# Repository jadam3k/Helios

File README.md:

# Helios

I'm 17 and I'm building a solar-powered watering system for a greenhouse. Helios has two custom boards: **MPPT** handles the power side, and **DRIVER2** handles the pumps, sensors, screen and buttons. I wanted a project where I could learn PCB design and embedded programming while making something useful for growing plants.

The repository includes the KiCad projects, local libraries, firmware, manufacturing files, BOMs and board previews. The watering rules are an example for my setup. You can change the code to suit different sensors or watering zones, after checking their electrical requirements.

| MPPT | DRIVER2 |
| --- | --- |
|  |  |
| [Board documentation](Boards/MPPT/README.md) | [Board documentation](Boards/DRIVER2/README.md) |
| [Preview video](media/helios-mppt-preview.mp4) | [Preview video](media/helios-driver-preview.mp4) |

The images and videos show the CAD designs. I haven't tested the assembled system yet.

## Current progress

| Part | What's implemented | What's been checked |
| --- | --- | --- |
| DRIVER2 | Pump control, watering schedule, START/STOP/manual buttons, sensor handling, LCD, RTC and FRAM | Firmware previously built in STM32CubeIDE. Testing with real pumps and sensors is still needed. |
| MPPT | Measurements, actual PWM, current/voltage regulation, output-power P&O, charge completion/restart, switched-load control and watchdogs | Both configurations compiled for STM32L072CZ with Arduino STM32 core 3.1.0. The portable tests passed 25 checks and checked 88 PWM duty settings in both timer directions. Hardware tests are still needed. |

The supplied MPPT profile is for **protected 3S Li-ion**, with a **12.55 V charge target** and a **2 A converter-output limit**. Charging stays off until the battery and calibration confirmations in `Config.h` are set. Read the [firmware setup instructions](Boards/MPPT/firmware/README.md) before changing those settings. This profile is not for 12 V AGM or 4S LiFePO4 batteries.

## How the boards connect

```mermaid
flowchart LR
    PANEL[Solar panel] --> MPPT[MPPT board]
    BAT[Protected 3S battery] <--> MPPT
    MPPT -->|Switched battery supply| DRIVER[DRIVER2 board]
    MPPT --> USB[5 V accessories]
    SENS[Sensors] --> DRIVER
    BUTTONS[START / STOP / manual] --> DRIVER
    DRIVER --> LCD[16x2 LCD]
    DRIVER --> PUMPS[Four pumps]
    DRIVER --> AUX[Three AUX outputs]
    DRIVER --> AO[Optional analog output]
```

Connect MPPT **U5 pin 1** to DRIVER2 **CN1 pin 2**, and MPPT **U5 pin 2** to DRIVER2 **CN1 pin 1**. DRIVER2 receives switched battery voltage, rather than a regulated 12 V supply. Check the operating voltage of the actual pumps, sensors and other loads across the battery's range. The MPPT XT30 output is on a separate, unswitched rail.

Each MCU runs its own firmware. There is no data connection between the two boards in this version. The 8P8C connector is unused and is not an Ethernet interface.

## Example watering behaviour

- START arms automatic watering. STOP takes priority. Holding the manual button runs all four pumps until it is released.
- The example checks scheduled watering at 07:00 and 19:00. It can also respond to dry soil, the temperature switch and air humidity when that input is enabled.
- Automatic watering runs all four pumps together. It stops when soil reaches the configured target, if soil readings go stale, on a fault, or after the 60-second runtime limit.
- The three AUX outputs have an optional five-second on/off demonstration. The analog output and USB data functions are unused in the example.
- My sensor setup uses a KSD9700 NO 35°C switch, a JXCT JXBS-3001-TR-RS soil sensor and a Ropam RHT-2H humidity sensor. The Ropam input is disabled in the supplied DRIVER2 code. Check the board instructions before enabling it.

The temperature switch only reports whether its threshold has been crossed. It doesn't return a temperature in degrees.

## What can be changed

DRIVER2 has four pump outputs, three AUX outputs, two analog sensor ports, two digital/pulse ports, two RS485 ports and an analog output. The RTC, FRAM, current-sense circuits, LCD and buttons can also be used by your own code.

For example, you could split watering into independent zones, add flow meters, use more Modbus sensors or write a local settings menu. Those are possible extensions, not features already included in the example. The MPPT code also exposes its measurements and operating state for debugging. Its optional UART2 telemetry requires access to PA2/PA3; no dedicated debug socket is fitted for those pins.

## Open and build

1. Open a board's `.kicad_pro` file in KiCad 10. Keep its local `libs/` folder and library tables next to it.
2. Import `Boards/DRIVER2/Filmware` into STM32CubeIDE to build the watering controller. The existing `Filmware` spelling is kept for compatibility with the project paths.
3. Open [HeliosMPPT.ino](Boards/MPPT/firmware/HeliosMPPT/HeliosMPPT.ino) in Arduino IDE 2. Install **STM32 MCU based boards 3.1.0**, select **Generic STM32L0 series → Generic L072CZTx**, and follow the [MPPT instructions](Boards/MPPT/firmware/README.md).
4. Follow [setup and wiring](docs/SETUP.md) for programming, configuration and the first hardware checks.

[Download the complete MPPT firmware](Boards/MPPT/firmware/HeliosMPPT-full.zip) · [Read all MPPT source files](Boards/MPPT/firmware/COMPLETE_SOURCE.txt) · [Build results](Boards/MPPT/firmware/BUILD_RESULTS.txt)

## Parts and cost

The [combined BOM](BOM.csv) includes both board lists and the external parts needed for an installation. Detailed tables are in the [DRIVER2 README](Boards/DRIVER2/README.md#bill-of-materials) and [MPPT README](Boards/MPPT/README.md#bill-of-materials). Both boards also keep their original manufacturing BOMs.

| Item | Quantity / cost status |
| --- | --- |
| DRIVER2 board components | 318 instances across 69 manufacturing-BOM rows |
| MPPT source components | 112 instances across 57 grouped rows, including test points |
| Priced subtotal | USD 185.5548, using priced rows from both boards, checked on November 19, 2026 |
| Full system cost | Incomplete: some MPPT parts, external devices, PCB fabrication, assembly, shipping and taxes are not priced |

The priced subtotal is not a full project quote. Missing costs are left blank or marked `n.a.` in the BOM. Some MPPT supplier selections are still missing. Final battery capacity, pump models, fuse selection and supplier quotes still need to be completed before ordering a full system.

## Power budget

Use actual measurements to size the panel and battery:

```text
Daily energy = standby power × 24 h + sum(load power × daily runtime)
Nominal battery energy = nominal battery voltage × capacity in Ah
```

As an example, 2 W standby plus four 6 W pumps running for ten minutes uses about **52 Wh/day**. A hypothetical 3S pack rated 11.1 V / 12 Ah stores about 133 Wh nominally. The usable energy is lower and depends on the cells, operating limits, temperature and losses. These numbers are examples, not measured Helios consumption or a final battery specification.

## Files

| Location | Contents |
| --- | --- |
| [Boards/MPPT/](Boards/MPPT/) | Power-board KiCad sources, libraries, firmware and documentation |
| [Boards/DRIVER2/](Boards/DRIVER2/) | Watering-controller KiCad sources, libraries and STM32CubeIDE project |
| [docs/SETUP.md](docs/SETUP.md) | Wiring, build and first-start instructions |
| [BOM.csv](BOM.csv) | Combined parts list and cost status |
| [CREDITS.md](CREDITS.md) | Development assistance and third-party dependencies |
| `media/` | Main renders and preview videos |

Source files are included for review and development. A project-wide license has not been selected. Third-party files keep their own license terms.

## A few thoughts at the end

I'm really happy with how Helios has turned out so far. This project taught me a lot about PCB design, power electronics and programming microcontrollers. It took a lot of hours, and there were plenty of things I had to learn along the way. Looking through the files now, it's nice to see how much work has come together. I hope it passes review and that the effort behind it comes through.

For anyone reviewing or analysing the project: I was given permission in **#PIXL-HELP** to use AI for translation. So yes, parts of the README and journals might have an "AI vibe" because AI helped translate them into English. I also received permission from staff in the same channel to write journals about the programming work. Development assistance is described in [CREDITS.md](CREDITS.md).

I also used AI to help create the 3D animations. Those animations were not included in my journals or counted towards my logged hours. The time spent preparing the BOM, writing the README and organising the project files was not included in my logged hours either.

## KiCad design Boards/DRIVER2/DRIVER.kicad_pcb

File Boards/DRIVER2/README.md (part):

# Helios DRIVER2

I designed this board to run the watering system in my Helios greenhouse project. The four-layer board is about 117 × 91 mm and uses an STM32F429ZGT6. It switches four 12 V pumps, has three spare 12 V outputs, and takes up to six sensors through M8 connectors. My example firmware uses three sensors. You can change the code for your own setup as long as your sensors match the port voltages and interfaces.

The firmware builds in STM32CubeIDE. I still need to test it on the board with real sensors and pumps.

[System overview](../../README.md) · [Wiring and setup](../../docs/SETUP.md) · [MPPT board](../MPPT/README.md)

## Project files

| File or folder | What's inside |
| --- | --- |
| [DRIVER.kicad_pro](DRIVER.kicad_pro) | Open this in KiCad 10. The schematic, board and design rules are next to it. |
| [libs/](libs/) | Local symbols, footprints and 3D models. Keep this folder next to the KiCad project. |
| [Schematic PDF](docs/DRIVER.pdf) · [STEP model](docs/DRIVER.step) | Schematic and mechanical model. |
| [production/](production/) | Gerber ZIP, BOM CSV, component positions and other fabrication files. |
| [Interactive BOM](bom/ibom.html) | Find parts on the board. |
| [Filmware/](Filmware/) | STM32CubeIDE project, CubeMX configuration, C source and STM32 HAL. |
| [Filmware.elf](Filmware/artifacts/Filmware.elf) | Debug build. |
| [3D preview](media/helios-driver-3d.png) · [Video](media/helios-driver-preview.mp4) | Board preview and video. |

## Hardware

| Block | Parts and purpose |
| --- | --- |
| Power | 12 V DC input, separate feeds for logic and loads, and 5 V and 3.3 V rails. |
| Pumps and AUX | Four PUMP and three AUX outputs. Each uses a TPS1H100B-Q1 high-side switch and has a current-sense circuit. Check pump startup current, supply capacity, wiring and board temperature under load. |
| Sensors | Six M8 ports. SENS1–2 are analog, SENS3–4 are digital or pulse inputs, and SENS5–6 use THVD1410 RS-485 transceivers. Pin 1 supplies 5 V on SENS1–4 and 12 V on SENS5–6. |
| AO1 | 0–10 V analog output with an OPA197. |
| Clock and memory | Battery-backed DS3231 RTC and FM24W256 FRAM on I²C1. |
| Display and controls | 16×2 LCD1602 with a PCF8574T backpack on I²C2, a level shifter, and a separate three-button connector. |
| Debug and supervision | SWD, power status inputs, TPS3431 watchdog, TPS3808 reset supervisor and USB-C. |

### Pinout

| Connector | Pins |
| --- | --- |
| CN1 | 1 GND, 2 +12 V DC. |
| CN8 / CN9 / CN7 / CN10 | PUMP1 / PUMP2 / PUMP3 / PUMP4. Pin 1 GND, pin 2 switched +12 V. |
| CN2 / CN3 / CN4 | AUX1 / AUX2 / AUX3. Pin 1 GND, pin 2 switched +12 V. |
| CN5 | Pin 1 GND, pin 2 AO1. |
| CN6 SWD | 1 VTref 3.3 V, 2 SWDIO, 3/5/9 GND, 4 SWCLK, 6 SWO, 10 NRST. |
| U12 LCD | JST-XH B4B-XH-A. 1 +5 V, 2 GND, 3 SDA, 4 SCL. Match the wires to the labels on your LCD module. |
| U10 buttons | 1 GND, 2 START (PF14), 3 STOP (PF15), 4 manual watering (PG0). Each momentary button shorts its input to GND when pressed. |
| M8 SENS1–6 | 1 power, 2 SIG2, 3 GND, 4 SIG1. For RS-485, pin 2 is B and pin 4 is A on this board. |

## Firmware

[main.c](Filmware/Core/Src/main.c) handles watering, the LCD, RTC, FRAM, sensor readings and outputs. [buttons.c](Filmware/Core/Src/buttons.c) handles the three buttons. The pin assignments and peripheral settings are in [Filmware.ioc](Filmware/Filmware.ioc).

- **START** arms automatic watering. **STOP** takes priority. Hold the third button to run all four pumps manually.
- The controller checks the schedule at **07:00 and 19:00**. Between those times it can also start if the soil reads 35% or less for five samples, the temperature switch stays closed for about 5 seconds, or air humidity is 40% or less once that input is enabled. Daytime watering requires a valid soil reading below 55% and a 30-minute cooldown between runs.
- Automatic watering runs all four pumps and stops after three consecutive soil readings of at least 55%, if the soil reading goes stale, or after 60 seconds. A power fault shuts off the outputs.
- Before starting a scheduled run, the firmware saves the date in FRAM. The morning and evening slots have separate CRC-checked records so a restart won't repeat a run. PE3 keeps FRAM write protection high between writes.
- The LCD uses I²C address `0x27` (7-bit) and switches pages every 4 seconds. To try the AUX demo, set `aux_demo_request = 1` in the debugger while stopped. The three AUX outputs switch every 5 seconds. STOP or a power fault ends the demo. The example leaves AO1 and USB data unused.

### Sensors in my setup

| Measurement | Sensor and port | Connection |
| --- | --- | --- |
| Temperature threshold | KSD9700 NO 35°C on SENS3 (DIGITAL 1) | Dry contact between SIG1 (pin 4) and GND (pin 3). The STM32 reads it on PD9. |
| Soil moisture | JXCT JXBS-3001-TR-RS on SENS5 (RS485 1) | Modbus RTU, address 1, 9600 baud, 8N1, register `0x0002`. USART2 uses PD5 for TX, PD6 for RX and PD4 for direction. [JXCT manual](https://sourcewell.in/wp-content/uploads/2022/08/RS485-Soil-Temperature-and-Humidity-Sensor-JX-Instruction-Manual.pdf) |
| Air humidity | Ropam RHT-2H, EAN 5907565617733, on SENS1 (ANALOG 1) | RH-10V goes to SIG1 (pin 4). Power the sensor from a separate 12 V feed with a shared GND. [Ropam manual](https://ropam.com.pl/wsparcie/wp-content/uploads/2018/09/rht-2_i_pl.pdf) |

## Build and setup

Import [Filmware](Filmware/) as an existing STM32CubeIDE project and build it. Keep the `Core`, `Drivers`, linker scripts and IDE project files together. The peripheral configuration is [Filmware.ioc](Filmware/Filmware.ioc). The existing `Filmware` folder spelling is intentional so the saved paths keep working.

Program through CN6 SWD using the pinout above. Check the RTC date/time, LCD address, sensor configuration and STOP behaviour before connecting the actual pumps. The firmware has been built, but I still need to test the assembled board with its sensors and loads.

The example uses three sensor ports. The other ports remain available for your own code. `AIR_RH_ENABLED` is 0 in the supplied source; leave it off until the Ropam input's voltage scaling is suitable and calibrated. Read [system setup](../../docs/SETUP.md) before powering DRIVER2 from MPPT: that connection carries battery voltage.

## Bill of materials

[Original manufacturing BOM](production/bom.csv) · [Combined system BOM](../../BOM.csv)

The tables use direct supplier product links. Prices are USD per component at the stated quantity tier, checked on **November 19, 2026**. Costs use the required component quantities; the final cart can cost more because of minimum order quantities. Shipping, tax, fabrication and assembly are separate.

| References | Qty | Board value | Manufacturer part | Supplier | USD/part | Price tier |
| --- | ---: | --- | --- | --- | ---: | ---: |
| BT1 | 1 | BS-2-1 | BS-2-1 | [C2895401](https://jlcpcb.com/partdetail/BS-2-1/C2895401) | — | — |
| C1, C11, C23, C25, C39, C62, C63, C70, C71, C82, C88 | 11 | 1uF | CL10A105KB8NNNC | [C15849](https://www.lcsc.com/product-detail/C15849.html) | 0.0093 | 50 |
| C10, C12, C13, C2, C20, C24, C27, C31, C33, C34, C36, C37, C38, C40, C41, C42, C43, C44, C45, C46, C47, C48, C5, C53, C55, C57, C58, C59, C60, C65, C66, C67, C68, C69, C72, C73, C74, C75, C76, C79, C8, C80, C81, C87, C89, C9, C92, C93 | 48 | 100nF | CC0603KRX7R9BB104 | [C14663](https://www.lcsc.com/product-detail/C14663.html) | 0.0061 | 100 |
| C14, C15, C21, C22, C32, C35, C83, C84, C85, C86, C94, C95, C96, C97 | 14 | 10nF | CL10B103KB8NNNC | [C1589](https://www.lcsc.com/product-detail/C1589.html) | 0.0071 | 50 |
| C16, C17, C18, C19, C28, C29 | 6 | 22uF | CL31A226KAHNNNE | [C12891](https://www.lcsc.com/product-detail/C12891.html) | 0.1038 | 20 |
| C26, C3, C30, C4, C6, C7, C77, C78, C90, C91 | 10 | 10uF | CL31A106KBHNNNE | [C13585](https://www.lcsc.com/product-detail/C13585.html) | 0.1238 | 10 |
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
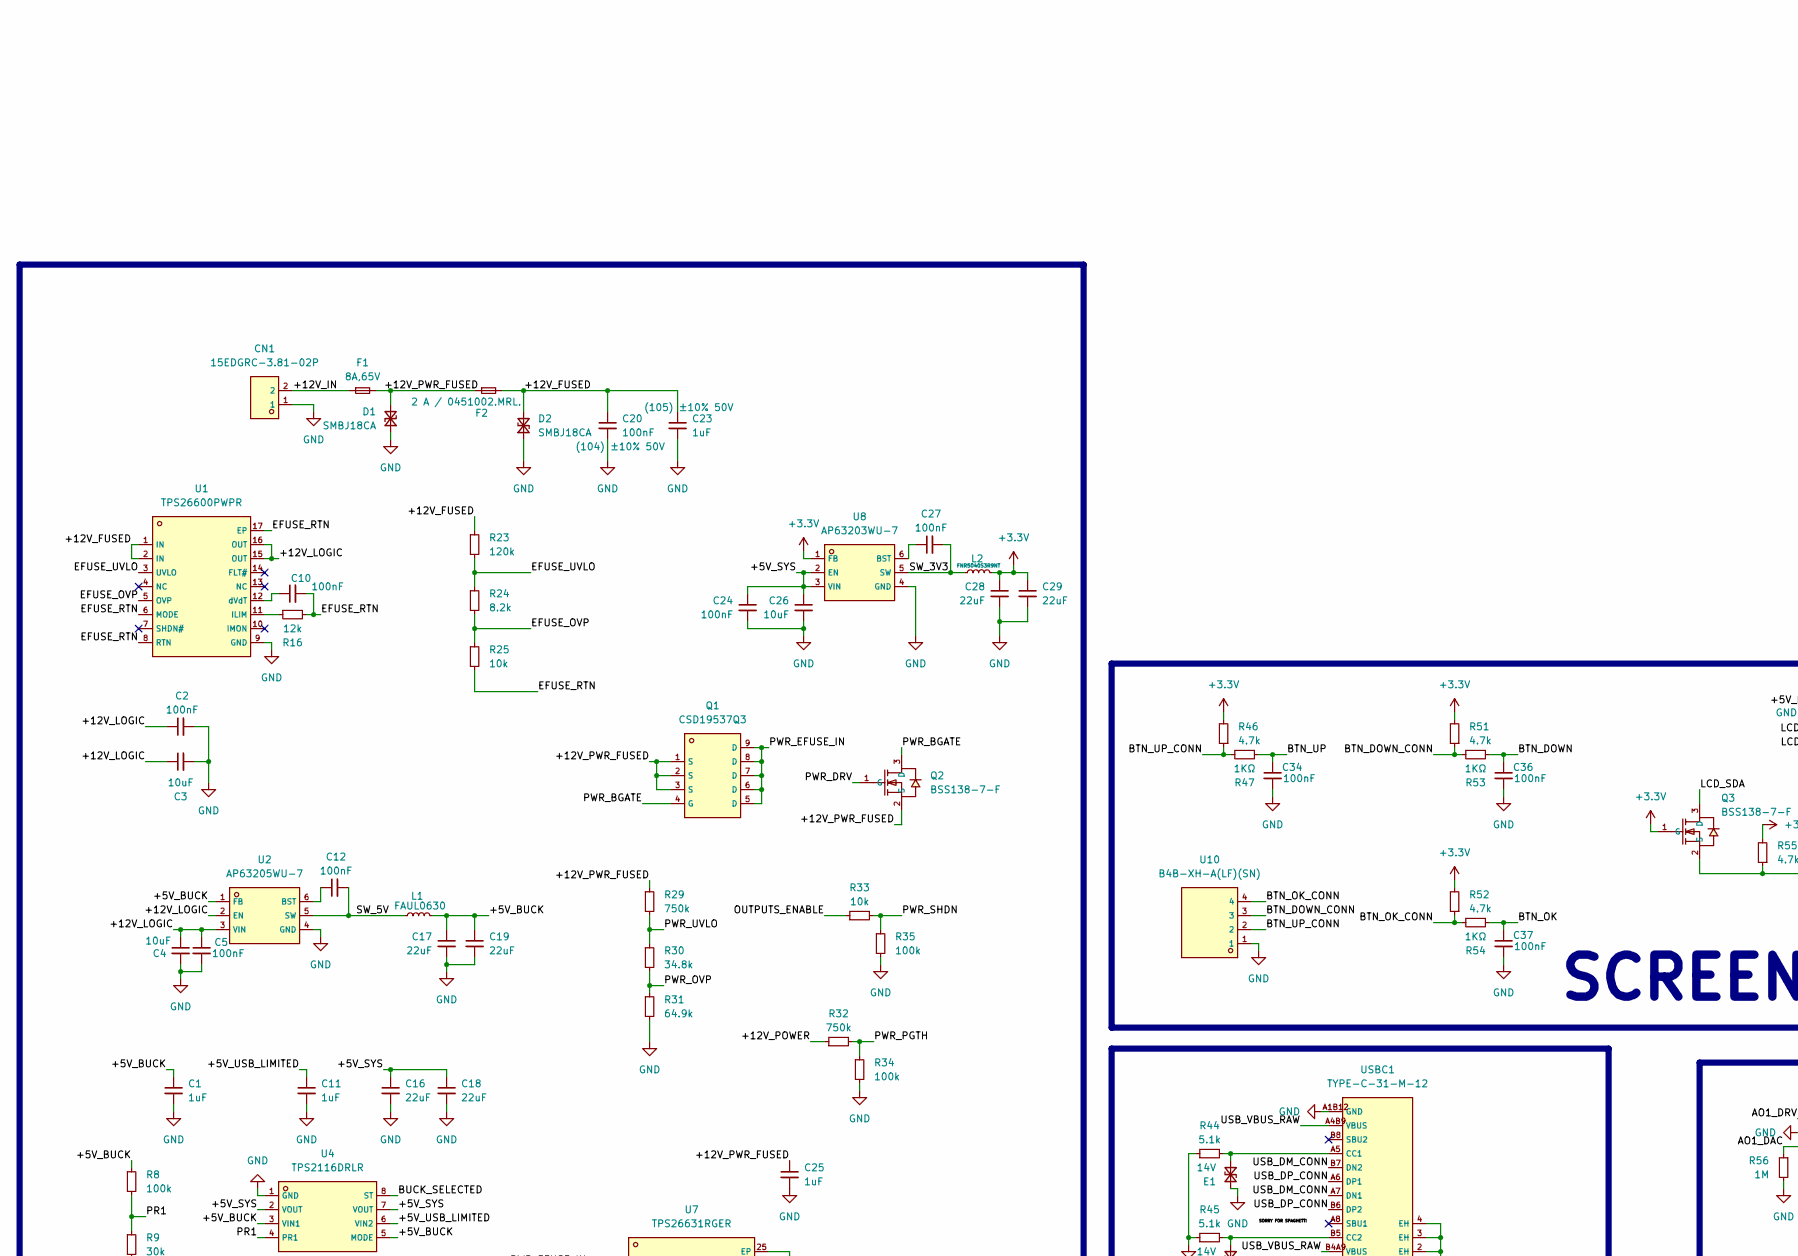
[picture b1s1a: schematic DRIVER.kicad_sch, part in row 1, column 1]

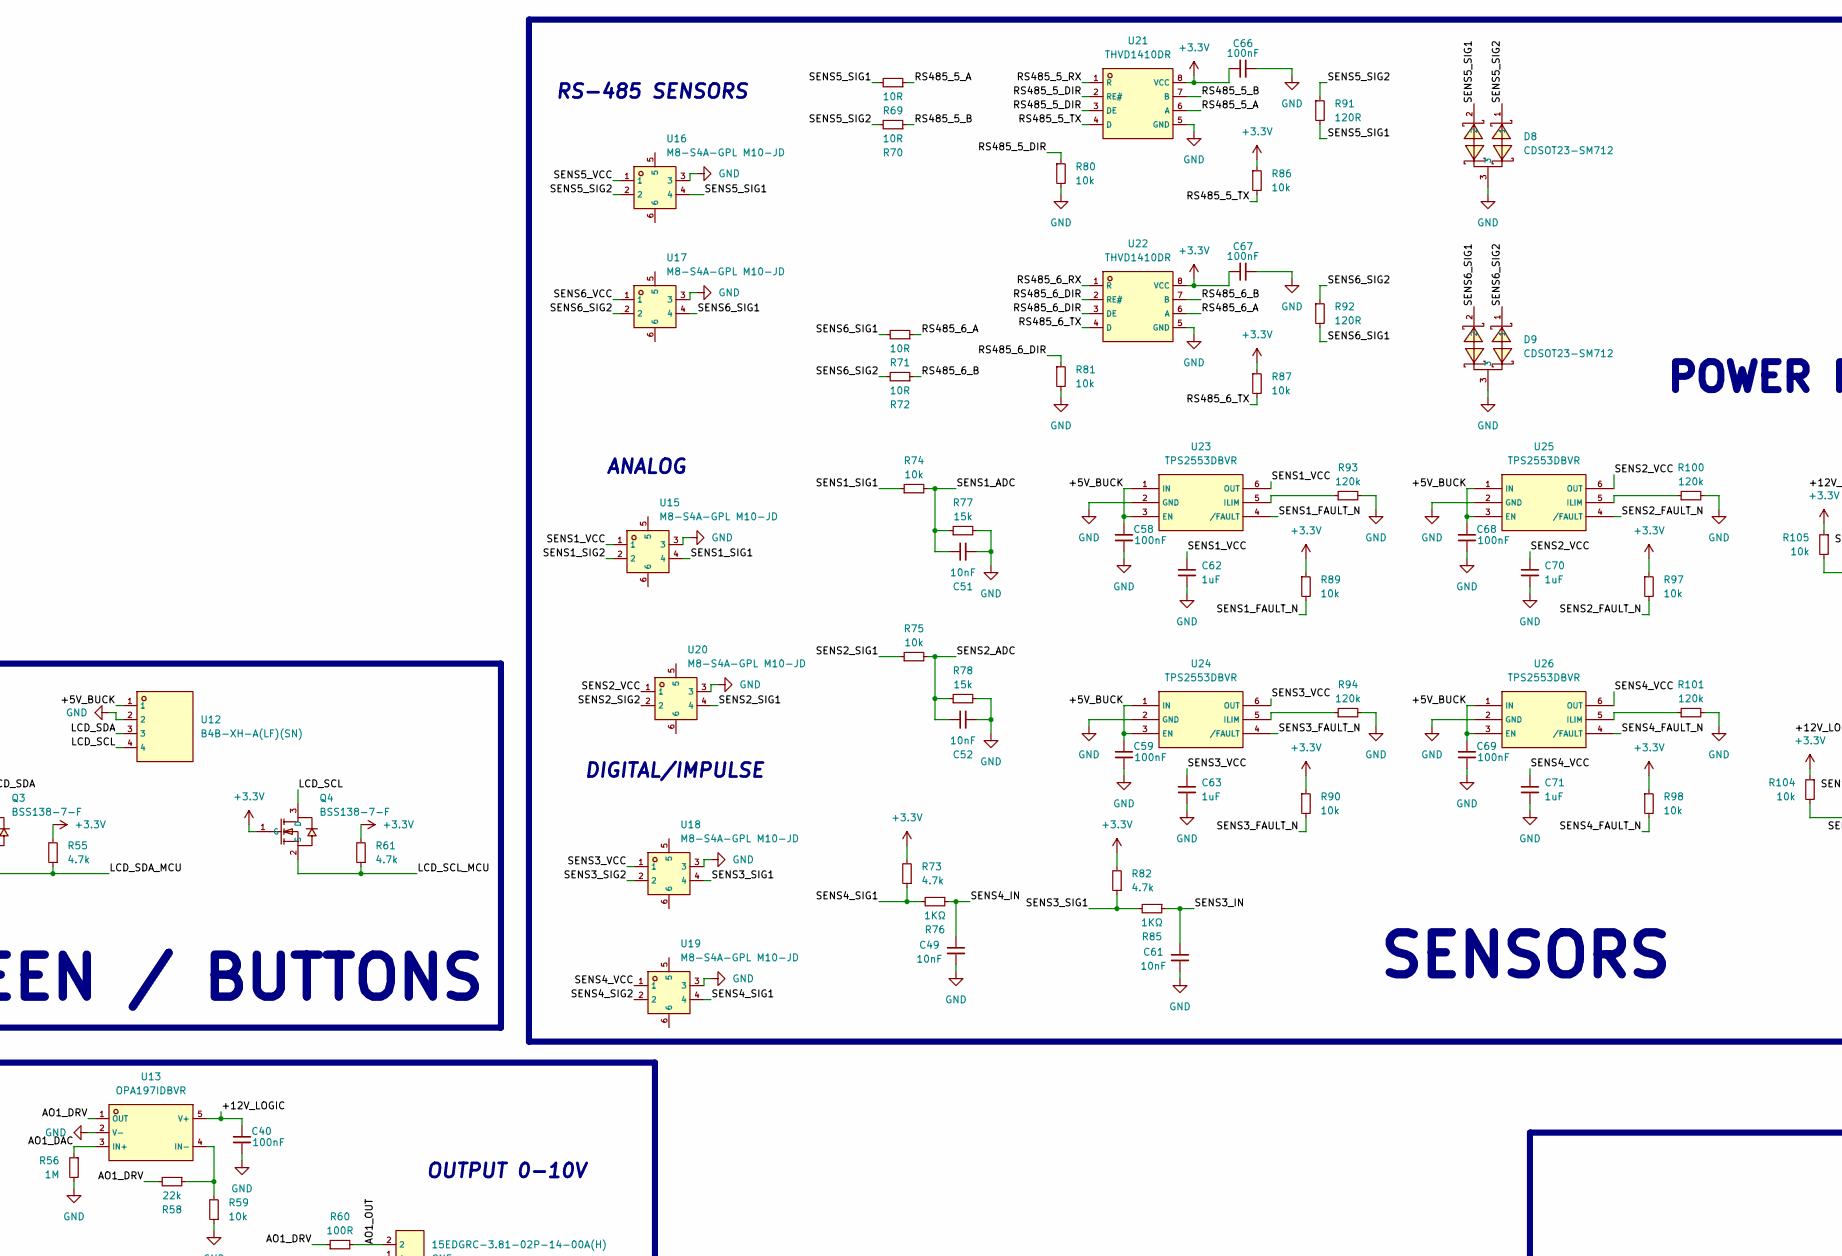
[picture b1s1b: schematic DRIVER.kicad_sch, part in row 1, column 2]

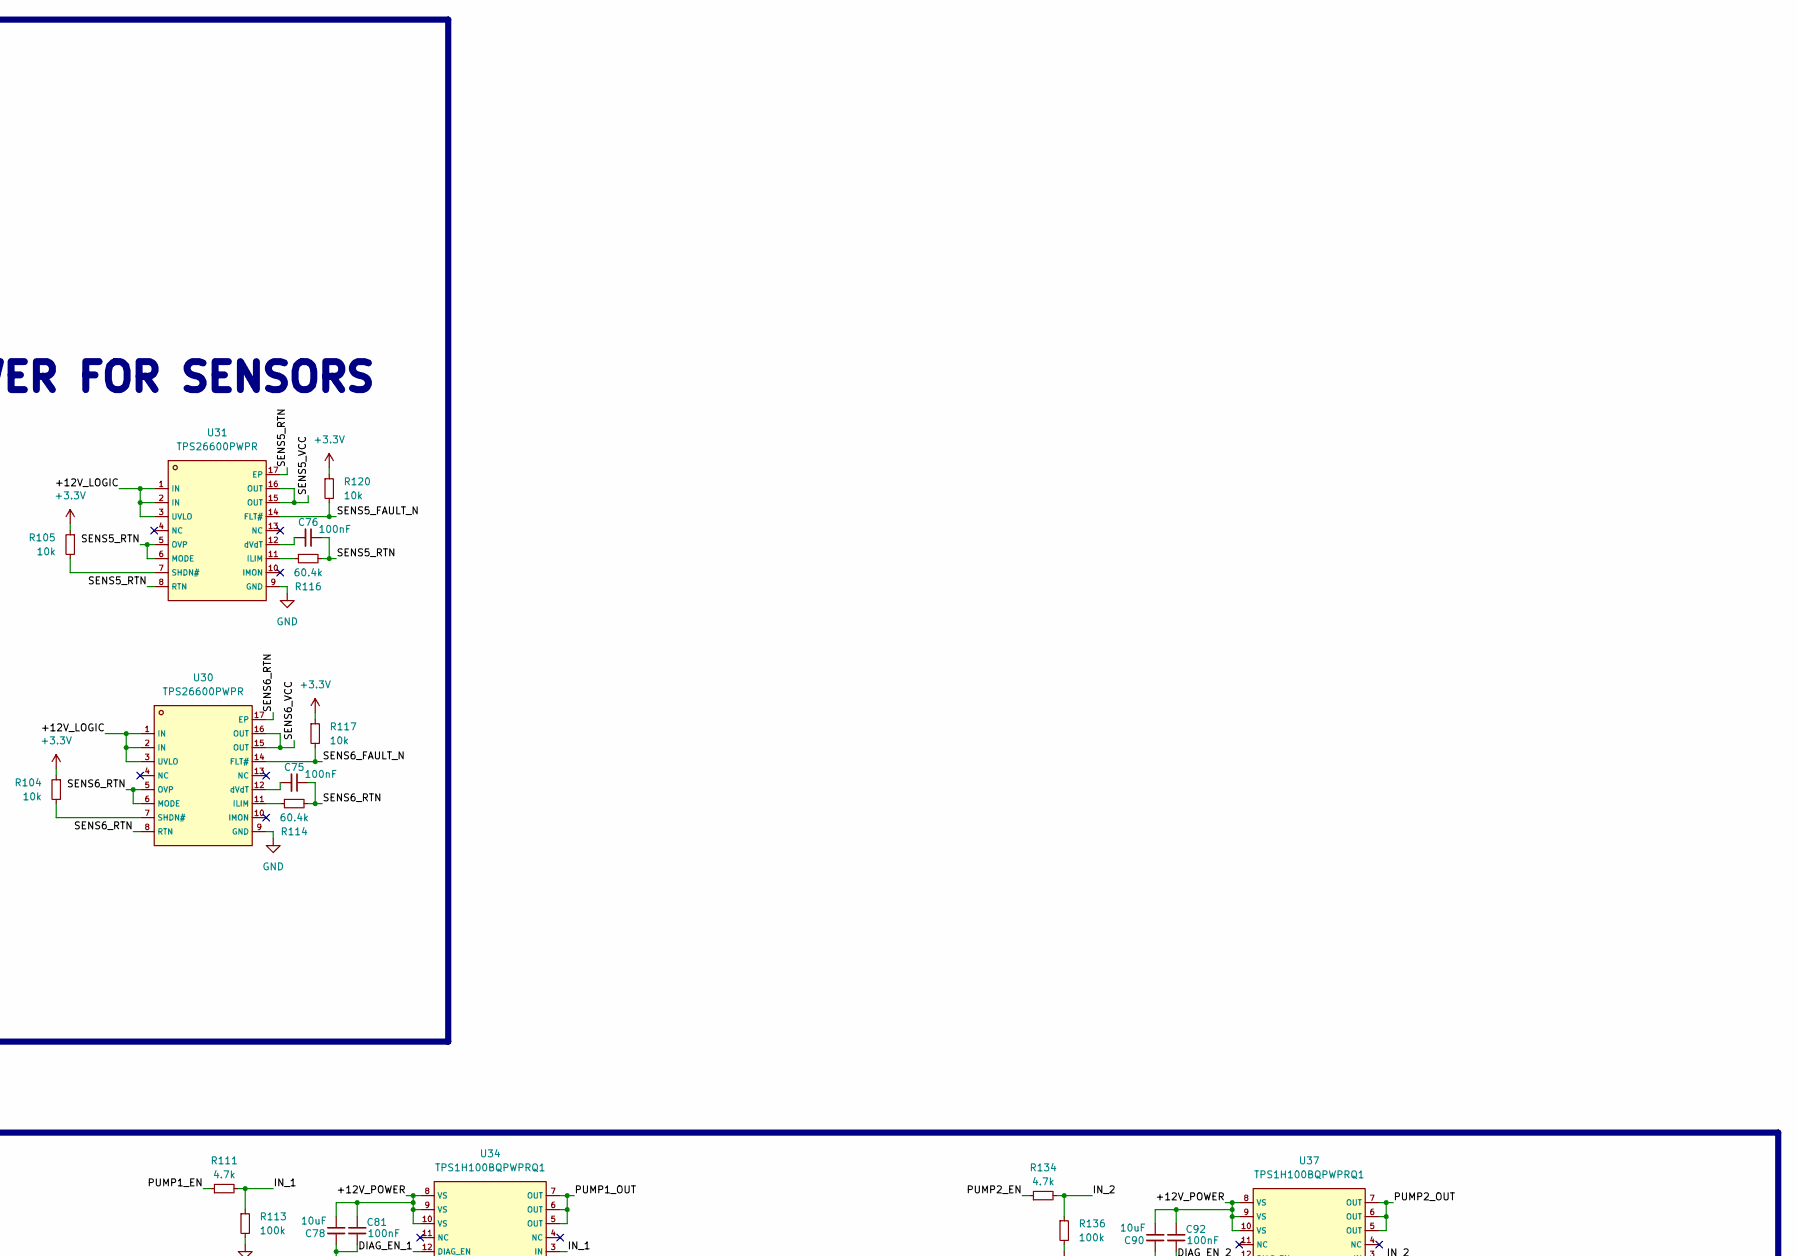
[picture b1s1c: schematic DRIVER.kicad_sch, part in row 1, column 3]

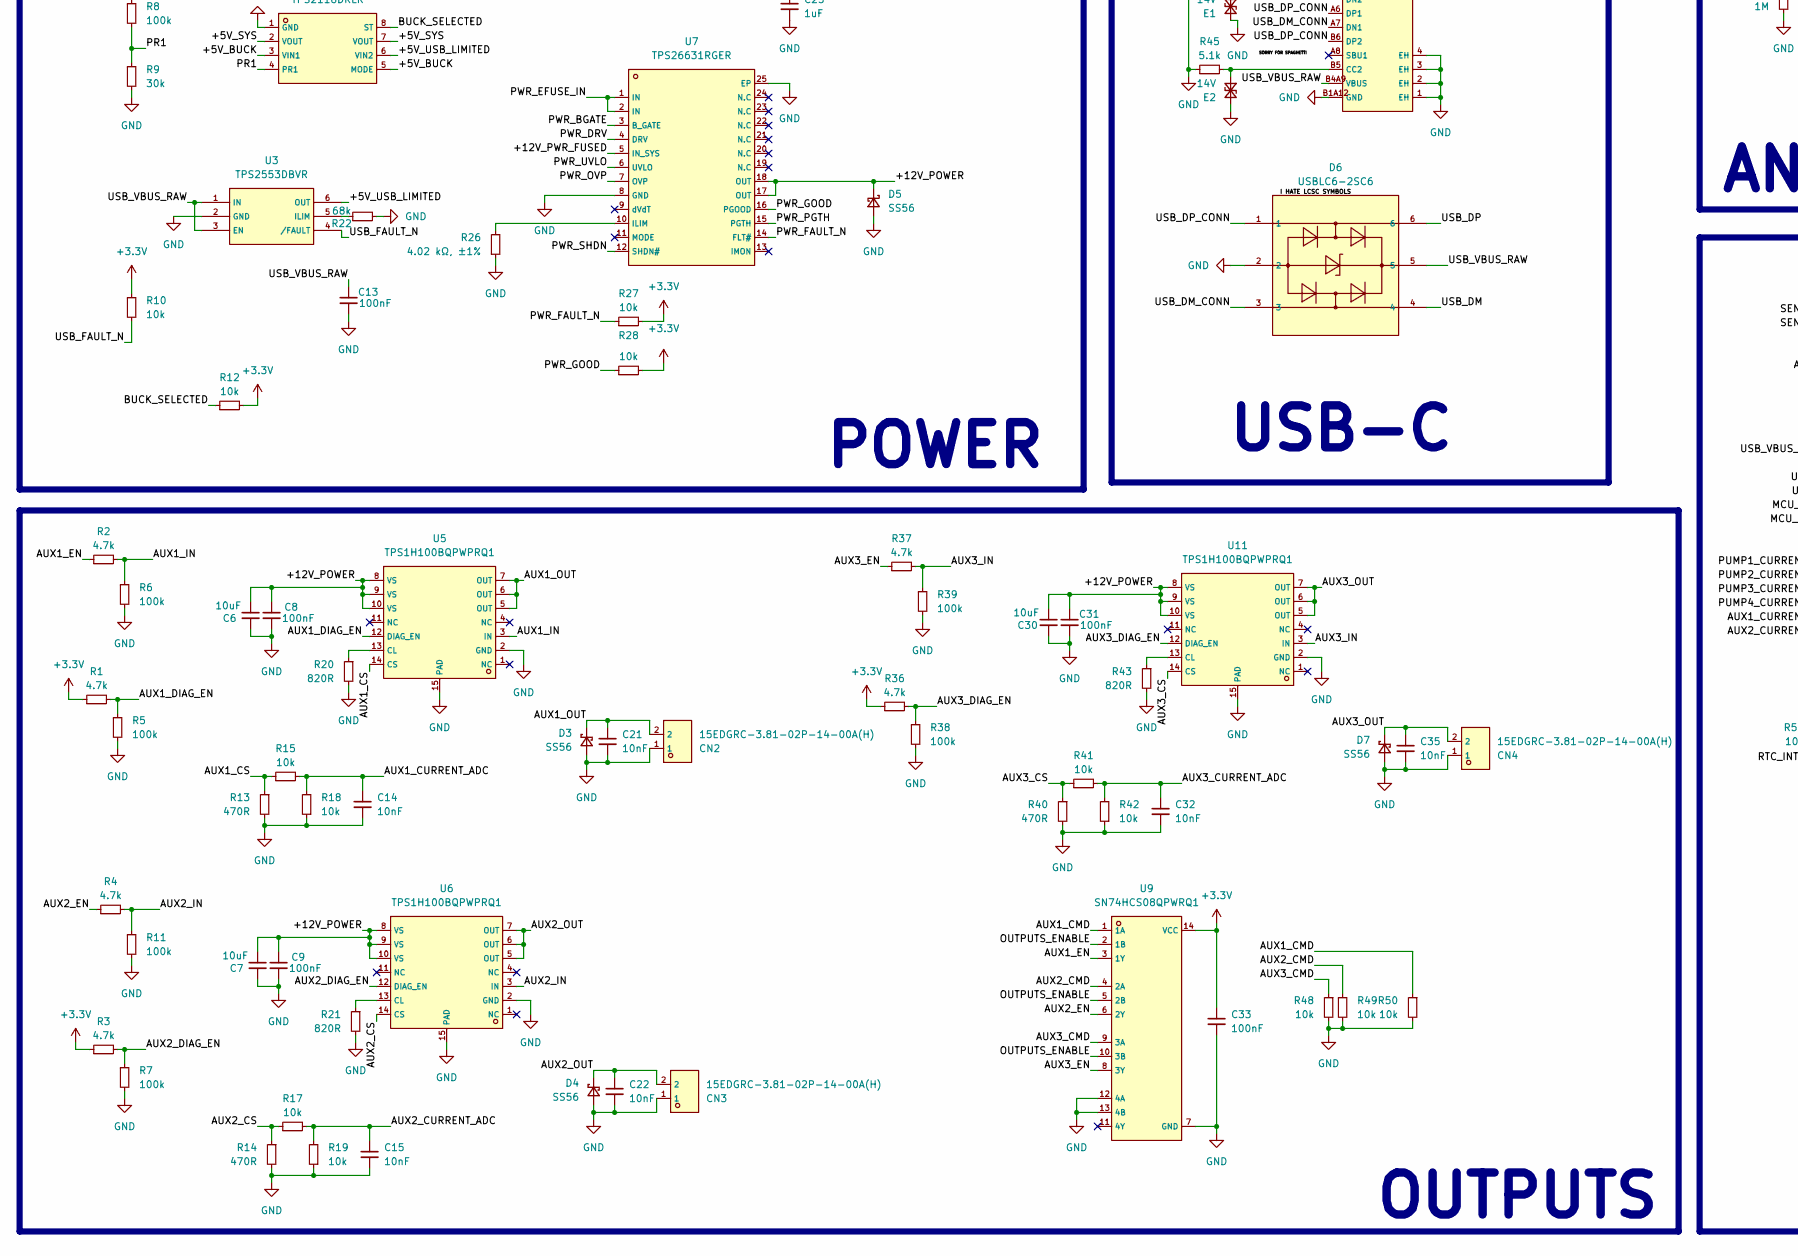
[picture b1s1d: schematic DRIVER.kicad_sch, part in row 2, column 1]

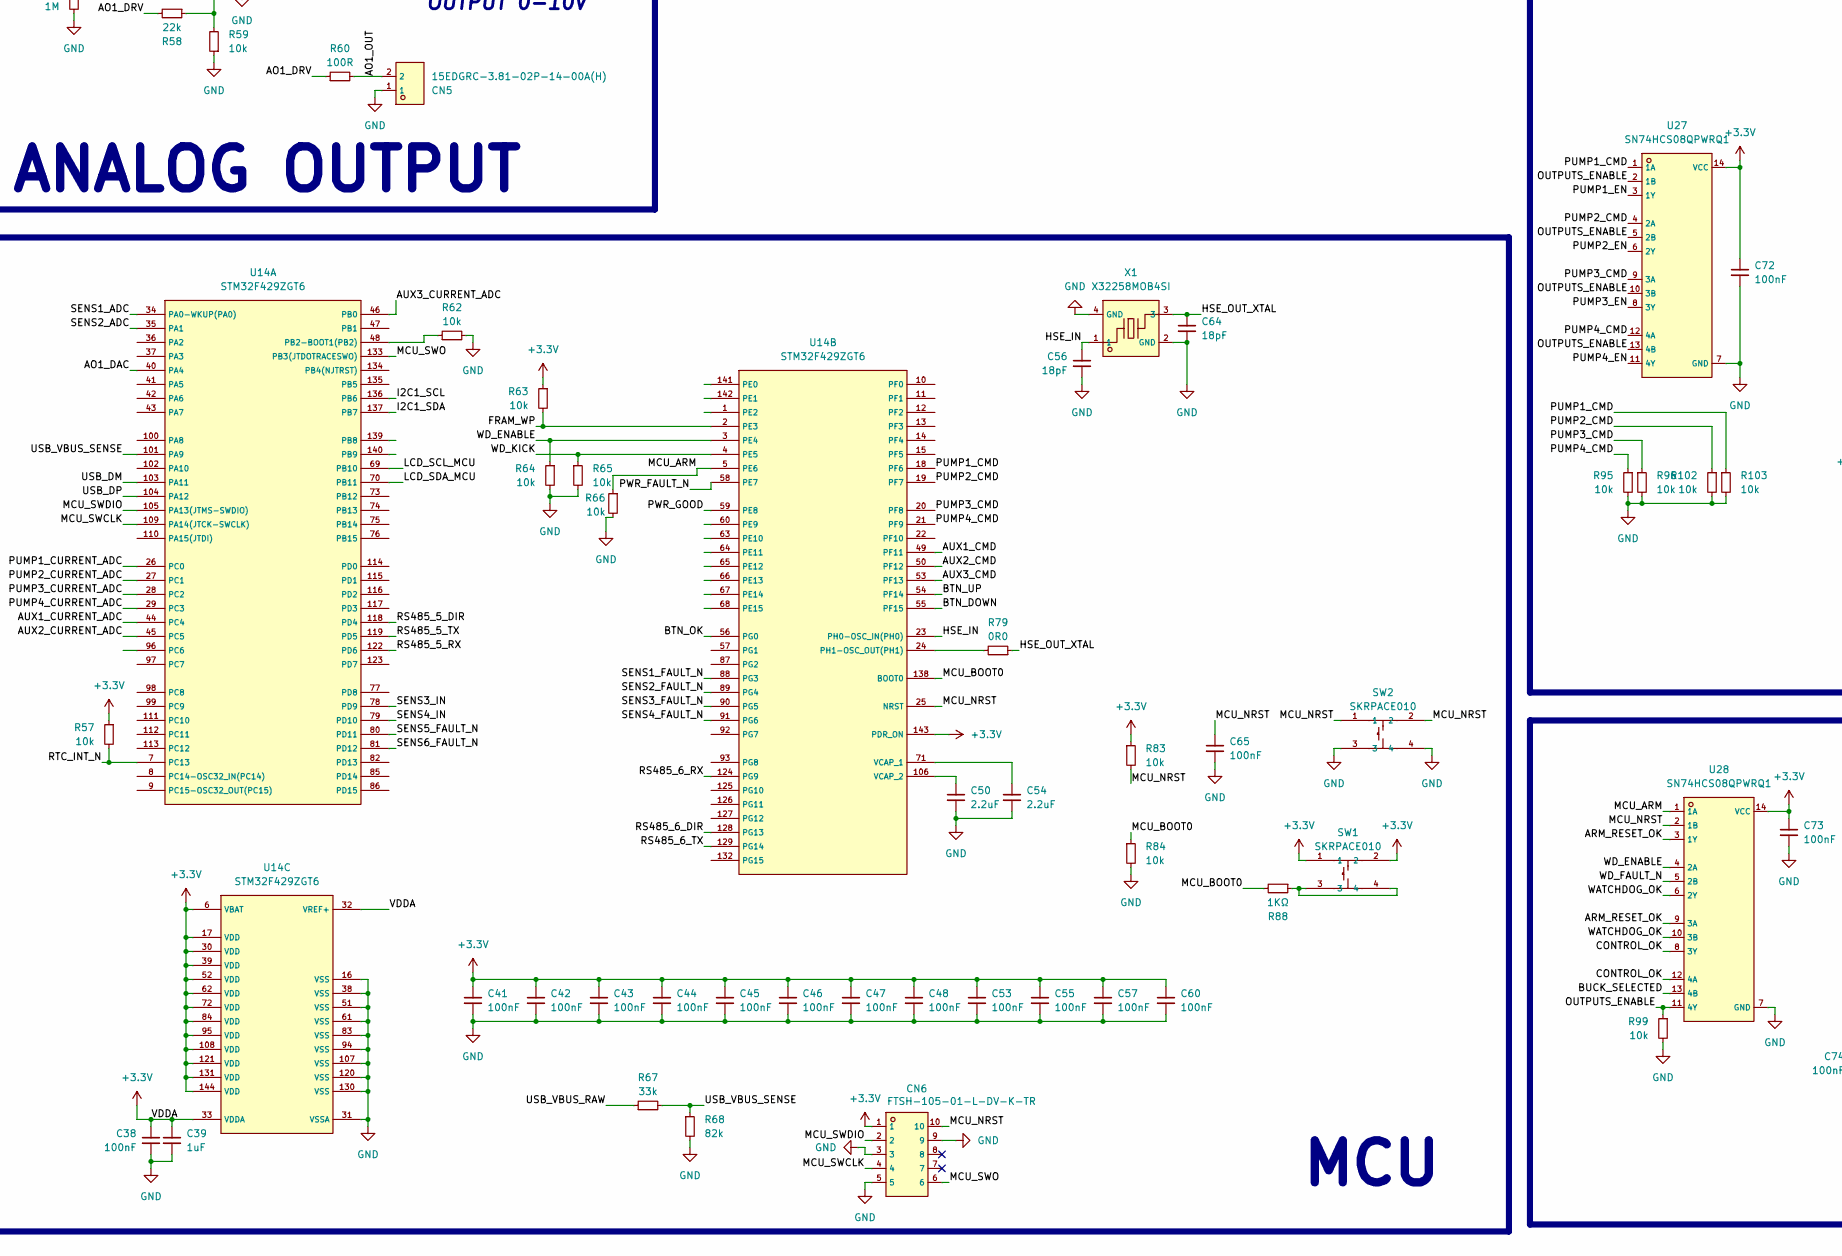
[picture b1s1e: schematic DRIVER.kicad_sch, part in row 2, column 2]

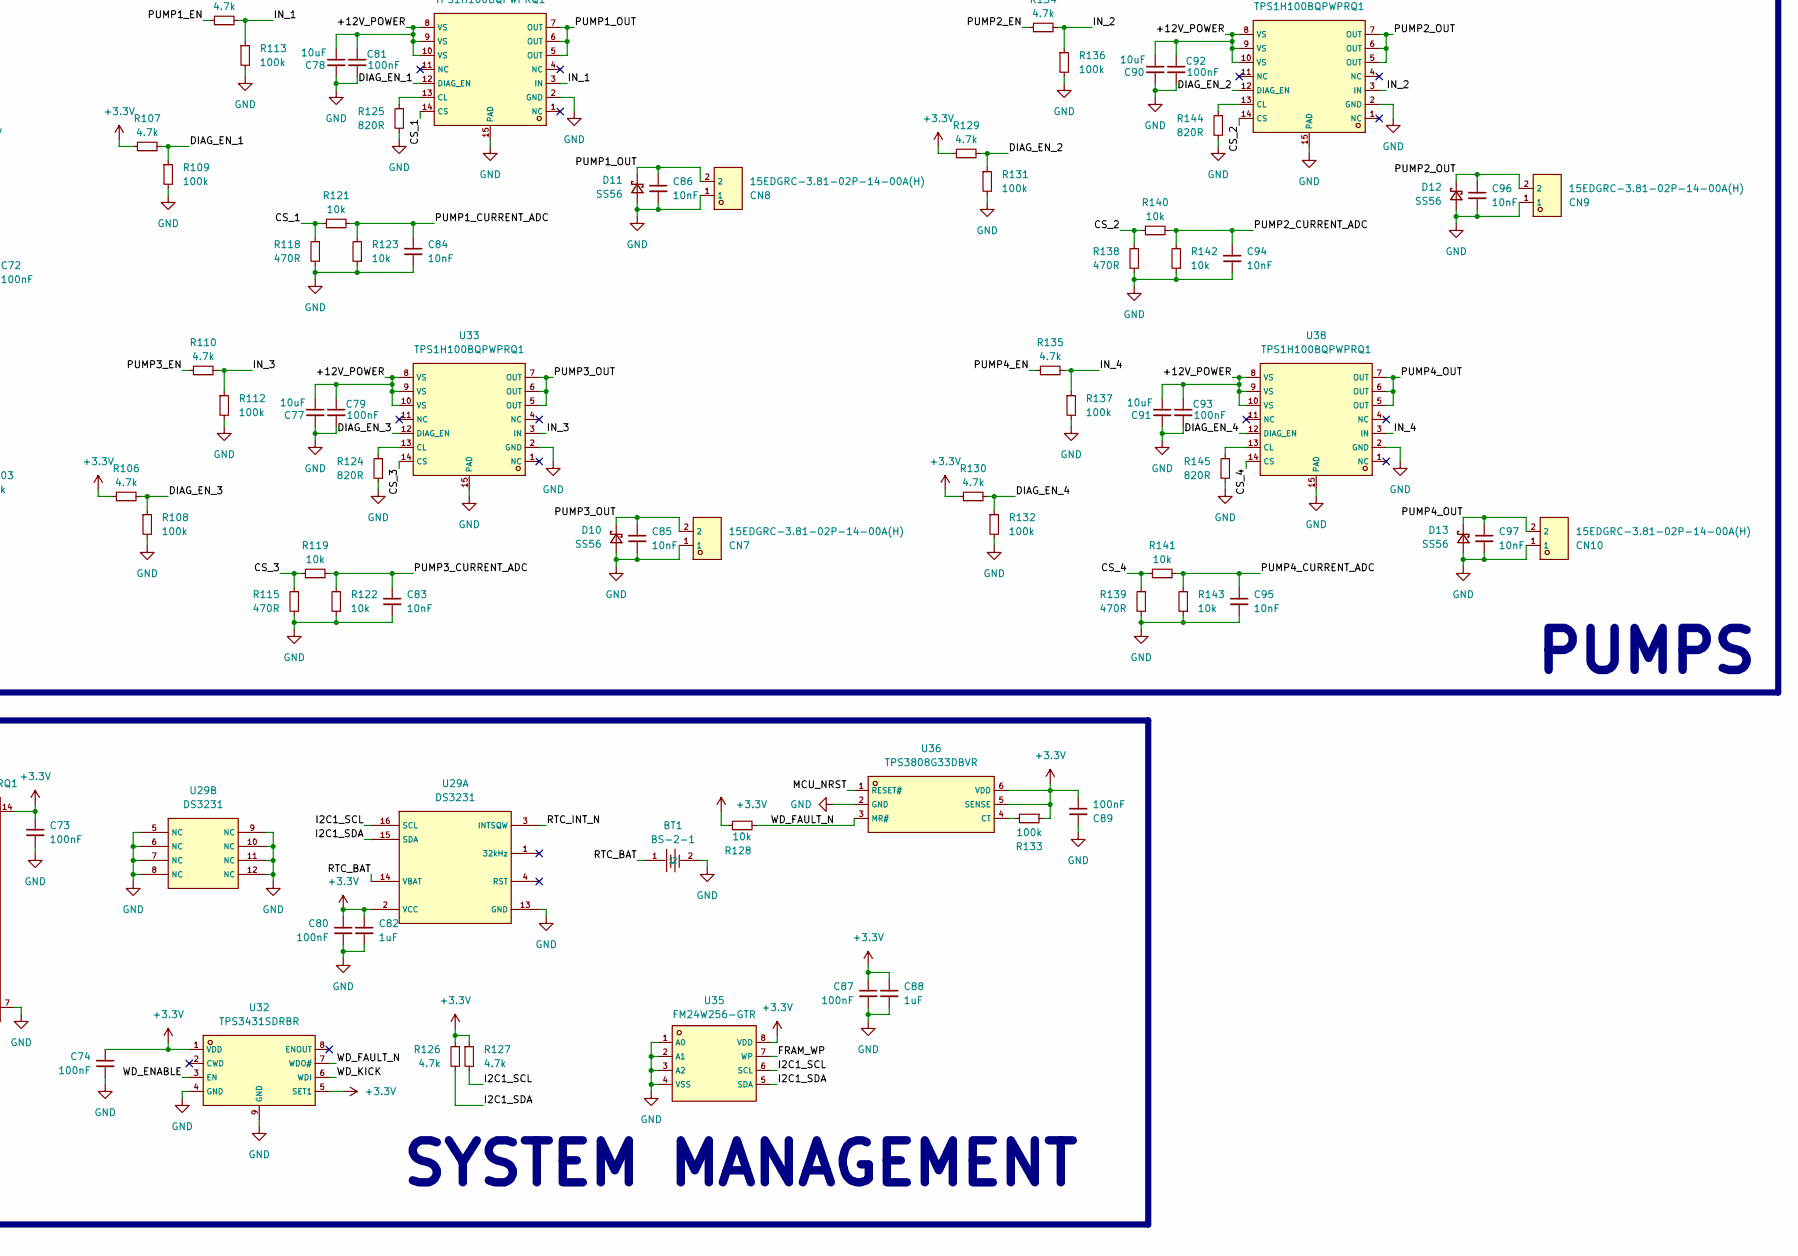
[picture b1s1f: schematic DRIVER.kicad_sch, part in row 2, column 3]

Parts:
BT1: BS-2-1; C2895401_BAT-TH_BS-2-1; LCSC C2895401
C1, C11, C23, C25, C39, C62, C63, C70, C71, C82, C88: 1uF; C15849_C0603; LCSC C15849
C2, C5, C8, C9, C10, C12, C13, C20, C24, C27, C31, C33, C34, C36, C37, C38, C40, C41, C42, C43, C44, C45, C46, C47, C48, C53, C55, C57, C58, C59, C60, C65, C66, C67, C68, C69, C72, C73, C74, C75, C76, C79, C80, C81, C87, C89, C92, C93: 100nF; C14663_C0603; LCSC C14663
C3, C4, C6, C7, C26, C30, C77, C78, C90, C91: 10uF; C13585_C1206; LCSC C13585
C14, C15, C21, C22, C32, C35, C83, C84, C85, C86, C94, C95, C96, C97: 10nF; C1589_C0603; LCSC C1589
C16, C17, C18, C19, C28, C29: 22uF; C12891_C1206; LCSC C12891
C49, C51, C52, C61: 10nF; C57112_C0603; LCSC C57112
C50, C54: 2.2uF; C1607_C0603; LCSC C1607
C56, C64: 18pF; C1647_C0603; LCSC C1647
CN1: 15EDGRC-3.81-02P; C507005_CONN-TH_2P-P3_81_JL15EDGRC-38102G01; LCSC C507005
CN2, CN3, CN4, CN5, CN7, CN8, CN9, CN10: 15EDGRC-3.81-02P-14-00A(H); C507005_CONN-TH_2P-P3_81_JL15EDGRC-38102G01; LCSC C507005
CN6: FTSH-105-01-L-DV-K-TR; C448647_CONN-SMD_FTSH-105-01-L-DV-K-TR; LCSC C448647
D1, D2: SMBJ18CA; C83327_SMB_L4_6-W3_6-LS5_3-BI; LCSC C83327
D3, D4, D5, D7, D10, D11, D12, D13: SS56; C65009_SMA_L4_3-W2_6-LS5_2-RD; LCSC C65009
D6: USBLC6-2SC6; C7519_SOT-23-6_L2_9-W1_6-P0_95-LS2_8-BL; LCSC C7519
D8, D9: CDSOT23-SM712; C404012_SOT-23_L2_9-W1_3-P1_90-LS2_4-BR; LCSC C404012
E1, E2: 14V; C84374_SOD-882_L1_0-W0_6-BI; LCSC C84374
F1: 8A,65V; C178980_FUSE-SMD_L6_1-W2_7; LCSC C178980
F2: 2 A / 0451002.MRL.; C99547_FUSE-SMD_L6_1-W2_7_0451002_MRL; LCSC C99547
L1: FAUL0630; C3040353_IND-SMD_L7_0-W6_6; LCSC C3040353
L2: FNR5040S3R9NT; C167962_IND-SMD_L5_0-W5_0_FNR50XXS; LCSC C167962
Q1: CSD19537Q3; C478469_DFN-8_L3_3-W3_3-P0_65-BL-3; LCSC C478469
Q2, Q3, Q4: BSS138-7-F; C40912_SOT-23-3_L2_9-W1_6-P1_90-LS2_8-BR; LCSC C40912
R1, R2, R3, R4, R36, R37, R46, R51, R52, R55, R61, R73, R82, R106, R107, R110, R111, R126, R127, R129, R130, R134, R135: 4.7k; C23162_R0603; LCSC C23162
R5, R6, R7, R8, R11, R34, R35, R38, R39, R108, R109, R112, R113, R131, R132, R133, R136, R137: 100k; C25803_R0603; LCSC C25803
R9: 30k; C22984_R0603; LCSC C22984
R10, R12, R15, R17, R18, R19, R25, R27, R28, R33, R41, R42, R48, R49, R50, R57, R59, R62, R63, R64, R65, R66, R74, R75, R80, R81, R83, R84, R86, R87, R89, R90, R95, R96, R97, R98, R99, R102, R103, R104, R105, R117, R119, R120, R121, R122, R123, R128, R140, R141, R142, R143: 10k; C25804_R0603; LCSC C25804
R13, R14, R40, R115, R118, R138, R139: 470R; C23179_R0603; LCSC C23179
R16: 12k; C22790_R0603; LCSC C22790
R20, R21, R43, R124, R125, R144, R145: 820R; C23253_R0603; LCSC C23253
R22: 68k; C23231_R0603; LCSC C23231
R23, R93, R94, R100, R101: 120k; C25808_R0603; LCSC C25808
R24: 8.2k; C25981_R0603; LCSC C25981
R26: 4.02 kΩ, ±1%; C23040_R0603; LCSC C23040
R29, R32: 750k; C23240_R0603; LCSC C23240
R30: 34.8k; C54531393_R0603; LCSC C54531393
R31: 64.9k; C14891_R0603; LCSC C14891
R44, R45: 5.1k; C23186_R0603; LCSC C23186
R47, R53, R54, R76, R85, R88: 1KΩ; C21190_R0603; LCSC C21190
R56: 1M; C22935_R0603; LCSC C22935
R58: 22k; C31850_R0603; LCSC C31850
R60: 100R; C35218_R2512; LCSC C35218
R67: 33k; C4216_R0603; LCSC C4216
R68: 82k; C23254_R0603; LCSC C23254
R69, R70, R71, R72: 10R; C313648_R0603; LCSC C313648
R77, R78: 15k; C22809_R0603; LCSC C22809
R79: 0R0; C21189_R0603; LCSC C21189
R91, R92: 120R; C22787_R0603; LCSC C22787
R114, R116: 60.4k; C2986234_R0402; LCSC C2986234
SW1, SW2: SKRPACE010; C139797_KEY-SMD_4P-L4_2-W3_2-P2_20-LS4_6; LCSC C139797
U1, U30, U31: TPS26600PWPR; C544399_HTSSOP-16_L5_0-W4_4-P0_65-LS6_4-BL-EP2_5; LCSC C544399
U2: AP63205WU-7; C2071056_TSOT-23-6_L2_9-W1_6-P0_95-LS2_8-BL; LCSC C2071056
U3, U23, U24, U25, U26: TPS2553DBVR; C55266_SOT-23-6_L2_9-W1_6-P0_95-LS2_8-BR; LCSC C55266
U4: TPS2116DRLR; C3235557_SOT-583-8_L2_1-W1_6-P0_50-LS1_6-BL; LCSC C3235557
U5, U6, U11, U33, U34, U37, U38: TPS1H100BQPWPRQ1; C475505_PDSO-G14_L5_0-W4_4-P0_65-LS6_4-BL-EP; LCSC C475505
U7: TPS26631RGER; C1850273_VQFN-24_L4_0-W4_0-P0_50-BL-EP2_5; LCSC C1850273
U8: AP63203WU-7; C780769_TSOT-26_L2_9-W1_6-P0_95-LS2_8-BL; LCSC C780769
U9, U27, U28: SN74HCS08QPWRQ1; C2867158_TSSOP-14_L4_9-W4_4-P0_65-LS6_4-BL; LCSC C2867158
U10, U12: B4B-XH-A(LF)(SN); C144395_CONN-TH_B4B-XH-A-LF-SN; LCSC C144395
U13: OPA197IDBVR; C221351_SOT-23-5_L3_0-W1_7-P0_95-LS2_8-BR; LCSC C221351
U14: STM32F429ZGT6; C46525_LQFP-144_L20_0-W20_0-P0_50-LS22_0-BL; LCSC C46525
U15, U16, U17, U18, U19, U20: M8-S4A-GPL M10-JD; C19108970_SMA-TH_M8-S4A-GPL-M10-JD; LCSC C19108970
U21, U22: THVD1410DR; C2671345_SOIC-8_L4_9-W3_9-P1_27-LS6_0-BL; LCSC C2671345
U29: DS3231; C9866_SOIC-16_L10_3-W7_5-P1_27-LS10_3-BL; LCSC C9866
U32: TPS3431SDRBR; C702145_VSON-8_L3_0-W3_0-P0_65-TL-EP; LCSC C702145
U35: FM24W256-GTR; C66020_SOIC-8_L4_9-W3_9-P1_27-LS6_0-BL; LCSC C66020
U36: TPS3808G33DBVR; C43698_SOT-23-6_L2_9-W1_6-P0_95-LS2_8-BR; LCSC C43698
USBC1: TYPE-C-31-M-12; C165948_USB-C_SMD-TYPE-C-31-M-12_1; LCSC C165948
X1: X32258MOB4SI; C2682775_CRYSTAL-SMD_4P-L3_2-W2_5-BL; LCSC C2682775

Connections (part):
+3.3V: C28.1, C29.1, C33.1, C38.1, C39.2, C41.1, C42.1, C43.1, C44.1, C45.1, C46.1, C47.1, C48.1, C53.1, C55.1, C57.1, C60.1, C66.2, C67.2, C72.1, C73.1, C74.1, C80.1, C82.2, C87.1, C88.2, C89.2, CN6.1, L2.2, Q3.1 (G), Q4.1 (G), R1.1, R3.1, R10.1, R12.2, R27.2, R28.2, R36.1, R46.2, R51.2, R52.2, R55.2, R57.1, R61.2, R63.1, R73.2, R82.2, R83.1, R86.1, R87.1, R89.1, R90.1, R97.1, R98.1, R104.1, R105.1, R106.1, R107.1, R117.1, R120.1, R126.1, R127.1, R128.1, R129.1, R130.1, R133.1, SW1.1, SW1.2, U8.1 (FB), U9.14 (VCC), U14.6 (VBAT), U14.17 (VDD), U14.30 (VDD), U14.32 (VREF+), U14.33 (VDDA), U14.39 (VDD), U14.52 (VDD), U14.62 (VDD), U14.72 (VDD), U14.84 (VDD), U14.95 (VDD), U14.108 (VDD), U14.121 (VDD), U14.131 (VDD)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
/+5V_BUCK: C1.2, C17.1, C19.1, C58.2, C59.2, C68.2, C69.2, L1.2, R8.1, U2.1 (FB), U4.3 (VIN1), U4.5 (MODE), U12.1, U23.1 (IN), U23.3 (EN), U24.1 (IN), U24.3 (EN), U25.1 (IN), U25.3 (EN), U26.1 (IN), U26.3 (EN)
/+5V_SYS: C16.1, C18.1, C24.1, C26.1, U4.2 (VOUT), U4.7 (VOUT), U8.2 (EN), U8.3 (VIN)
/+5V_USB_LIMITED: C11.2, U3.6 (OUT), U4.6 (VIN2)
/+12V_FUSED: C20.1, C23.2, D2.2 (A2), F2.2, R23.1, U1.1 (IN), U1.2 (IN)
/+12V_IN: CN1.2, F1.1
/+12V_LOGIC: C2.1, C3.1, C4.2, C5.2, C40.2, U1.15 (OUT), U1.16 (OUT), U2.2 (EN), U2.3 (VIN), U13.5 (V+), U30.1 (IN), U30.2 (IN), U30.3 (UVLO), U31.1 (IN), U31.2 (IN), U31.3 (UVLO)
/+12V_POWER: C6.2, C7.2, C8.2, C9.2, C30.2, C31.2, C77.2, C78.2, C79.2, C81.2, C90.2, C91.2, C92.2, C93.2, D5.1 (K), R32.1, U5.8 (VS), U5.9 (VS), U5.10 (VS), U6.8 (VS), U6.9 (VS), U6.10 (VS), U7.17 (OUT), U7.18 (OUT), U11.8 (VS), U11.9 (VS), U11.10 (VS), U33.8 (VS), U33.9 (VS), U33.10 (VS), U34.8 (VS), U34.9 (VS), U34.10 (VS), U37.8 (VS), U37.9 (VS), U37.10 (VS), U38.8 (VS), U38.9 (VS), U38.10 (VS)
/+12V_PWR_FUSED: C25.2, D1.2 (A2), F1.2, F2.1, Q1.1 (S), Q1.2 (S), Q1.3 (S), Q2.2 (S), R29.1, U7.5 (IN_SYS)
/AO1_DAC: R56.1, U13.3 (IN+), U14.40 (PA4)
/AO1_DRV: R58.2, R60.1, U13.1 (OUT)
/AO1_OUT: CN5.2, R60.2
/ARM_RESET_OK: U28.3 (1Y), U28.9 (3A)
/AUX1_CMD: R50.1, U9.1 (1A), U14.49 (PF11)
/AUX1_CS: R13.1, R15.1, U5.14 (CS)
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
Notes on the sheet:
POWER FOR SENSORS
SYSTEM MANAGEMENT
ANALOG
ANALOG OUTPUT
SCREEN / BUTTONS
USB-C
RS-485 SENSORS
PUMPS
OUTPUTS
MCU
SENSORS
DIGITAL/IMPULSE
POWER
OUTPUT 0-10V

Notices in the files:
Boards/DRIVER2/README.md:
U15, U16, U17, U18, U19, U20 | 6 | M8-S4A-GPL M10-JD | M8-S4A-GPL M10-JD | [C19108970](https://www.lcsc.com/product-detail/C19108970.html) | 5.0907 | 1
parts and their libraries:
https://wmsc.lcsc.com/wmsc/upload/file/pdf/v2/lcsc/2311011001_CAZN-M8-S4A-GPL-M10-JD_C19108970.pdf
